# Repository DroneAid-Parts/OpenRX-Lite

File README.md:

# DroneAid OpenRX Lite

Open-source 2.4 GHz ExpressLRS receiver for small FPV aircraft. DroneAid OpenRX Lite
combines an ESP32-C3 and SX1281 with an on-board ceramic link antenna in a
10.0 x 11.5 mm board.

## Specifications

| | |
|---|---|
| Band | 2.4 GHz |
| Radio | SX1281 |
| Antenna | On-board ceramic |
| Telemetry power | 13 dBm (20 mW) |
| Protocol | CRSF |
| MCU | ESP32-C3 |
| Input | 5 V pad |
| Firmware | ExpressLRS |
| Flashing | Betaflight passthrough or Wi-Fi |
| Dimensions | 10.0 x 11.5 mm |
| PCB | 6-layer, 1.0 mm |

Technical write-up, part list and layout constraints: [AGENTS.md](AGENTS.md).

## In the line

What pairs with what, and what is available:
[opendrone.be](https://opendrone.be).

## Contributing

See [CONTRIBUTING.md](CONTRIBUTING.md).

## License

Hardware licensed under [CERN-OHL-S-2.0](https://ohwr.org/cern_ohl_s_v2.txt),
see [LICENSE](LICENSE).

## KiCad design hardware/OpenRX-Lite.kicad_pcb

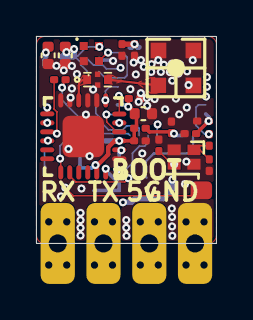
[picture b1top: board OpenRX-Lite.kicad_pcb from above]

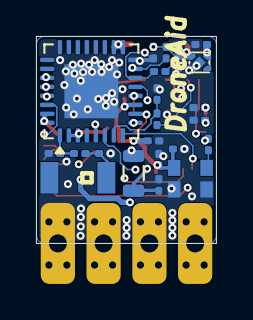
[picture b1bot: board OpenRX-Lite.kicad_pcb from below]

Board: 6 copper layers, 10.0 x 11.5 mm, 47 parts (22 on the bottom side), 28 nets.

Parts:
AE1: 2450AT18A100E; ANT-SMD_L3.2-W1.6
AE2: 47948-0001; ANT-SMD_47948-0001
C1, C3: 15pF; C_0201_0603Metric
C4, C10, C15, C23, C25, C28: 1uF; C_0201_0603Metric
C5, C6, C9, C12, C13, C14, C17: 100nF; C_0201_0603Metric
C8, C11, C16: 10uF; C_0402_1005Metric
C19: 1nF; C_0201_0603Metric
C20: 470nF; C_0201_0603Metric
C21, C22: 1.2pF; C_0201_0603Metric
C24, C26, C27: 10nF; C_0201_0603Metric
D1: XL-1010RGBC-WS2812B; LED-SMD_4P-L1.0-W1.0-TL_XL-1010RGBC-WS2812B
FL1: 2450FM07D0034T; FILTER-SMD_4P-L1.0-W0.5-L
L1: 24nH; L_0201_0603Metric
L2: 2.5nH; L_0201_0603Metric
L3: 2.0nH; L_0201_0603Metric
L4: 15uH; L_0805_2012Metric
OSC1: OW7EL89CENUNFAYLC-52M; OSC-SMD_4P-L2.0-W1.6-BL_TXC_7Z
R2, R3, R4, R5: 10k; R_0201_0603Metric
TP1: RX; SolderPad_1.2x2.0mm
TP2: TX; SolderPad_1.2x2.0mm
TP3: 5V; SolderPad_1.2x2.0mm
TP4: GND; SolderPad_1.2x2.0mm
TP5: BOOT; SolderPad_1.2x2.0mm
U1: ESP32-C3; QFN-32-1EP_5x5mm_P0.5mm_EP3.7x3.7mm
U2: TLV75533PDQNR; X2SON-4_L1.0-W1.0-P0.65-TL-EP
U3: SX1281IMLTRT; QFN-24_L4.0-W4.0-P0.50-TL-EP2.6
X1: CJ17-400001010B20; CRYSTAL-SMD_4P-L1.6-W1.2-BL

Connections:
+3V3: C4.1, C5.1, C6.1, C9.1, C11.1, C12.1, C13.1, C14.1, C15.1, C16.1, C17.1, C23.1, C24.1, D1.2 (VDD), L3.2, OSC1.4 (VDD), R2.1, R3.1, R4.1, R5.2, U1.11 (VDD3P3_RTC), U1.17 (VDD3P3_CPU), U1.18 (VDD_SPI), U1.31 (VDDA), U1.32 (VDDA), U2.1 (OUT), U3.11 (VBAT_IO), U3.15 (VBAT)
+5V: C8.1, C10.1, TP3.1 (1_1), U2.3 (EN), U2.4 (IN)
/ESP32-C3 + SX1281 Core (UFL)/BOOT: R4.2, TP5.1 (1_1), U1.15 (GPIO9)
/ESP32-C3 + SX1281 Core (UFL)/BUSY: U1.8 (GPIO3), U3.7 (BUSY)
/ESP32-C3 + SX1281 Core (UFL)/CHIP_EN: C28.1, R5.1, U1.7 (CHIP_EN)
/ESP32-C3 + SX1281 Core (UFL)/DIO1: U1.5 (XTAL_32K_N), U3.8 (DIO1)
/ESP32-C3 + SX1281 Core (UFL)/LED: D1.4 (DIN), R3.2, U1.14 (GPIO8)
/ESP32-C3 + SX1281 Core (UFL)/MISO: U1.10 (MTDI), U3.16 (MISO_TX)
/ESP32-C3 + SX1281 Core (UFL)/MOSI: U1.9 (MTMS), U3.17 (MOSI_RX)
/ESP32-C3 + SX1281 Core (UFL)/NSS: U1.13 (MTDO), U3.19 (NSS_CTS)
/ESP32-C3 + SX1281 Core (UFL)/RST: R2.2, U1.6 (GPIO2), U3.3 (NRESET)
/ESP32-C3 + SX1281 Core (UFL)/SCK: U1.12 (MTCK), U3.18 (SCK_RTSN)
/ESP32-C3 + SX1281 Core (UFL)/WIFI: AE1.1, C21.1, L2.1
/ESP32-C3 + SX1281 Core (UFL)/XTAL_N: C3.1, U1.29 (XTAL_N), X1.3
/ESP32-C3 + SX1281 Core (UFL)/XTAL_P: L1.2, U1.30 (XTAL_P)
GND: AE2.1, AE2.2, AE2.4, C1.2, C3.2, C4.2, C5.2, C6.2, C8.2, C9.2, C10.2, C11.2, C12.2, C13.2, C14.2, C15.2, C16.2, C17.2, C20.1, C21.2, C22.2, C23.2, C24.2, C25.2, C26.1, C27.2, C28.2, D1.3 (GND), FL1.2 (GND), FL1.4 (GND), OSC1.1 (GND), OSC1.2 (GND), TP4.1 (1_1), U1.16 (GPIO10), U1.33 (GND), U2.2 (GND), U2.5 (EP), U3.13 (GND), U3.20 (GND), U3.21 (GND), U3.23 (GND), U3.24 (GND), U3.25 (EP), X1.2 (GND), X1.4 (GND)
unnamed: C1.1, L1.1, X1.1
unnamed: C25.1, L3.1, U1.2 (VDD3P3), U1.3 (VDD3P3)
unnamed: FL1.1 (IN), U3.22 (RFIO)
unnamed: AE2.3, FL1.3 (OUT)
unnamed: C19.1, OSC1.3 (Out_Put)
unnamed: C22.1, L2.2, U1.1 (LNA_IN)
unnamed: TP1.1 (1_1), U1.27 (U0RXD)
unnamed: TP2.1 (1_1), U1.28 (U0TXD)
unnamed: C20.2, C26.2, L4.1, U3.2 (VDD_IN), U3.12 (DCC_FB)
unnamed: L4.2, U3.14 (DCC_SW)
unnamed: C27.1, U3.1 (VR_PA)
unnamed: C19.2, U3.4 (XTA)
